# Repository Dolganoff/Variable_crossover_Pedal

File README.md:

Variable_crossover_Pedal
========================

Variable crossover Pedal
For more details refer to http://www.dolganoff.com/fr/tag/crossover/

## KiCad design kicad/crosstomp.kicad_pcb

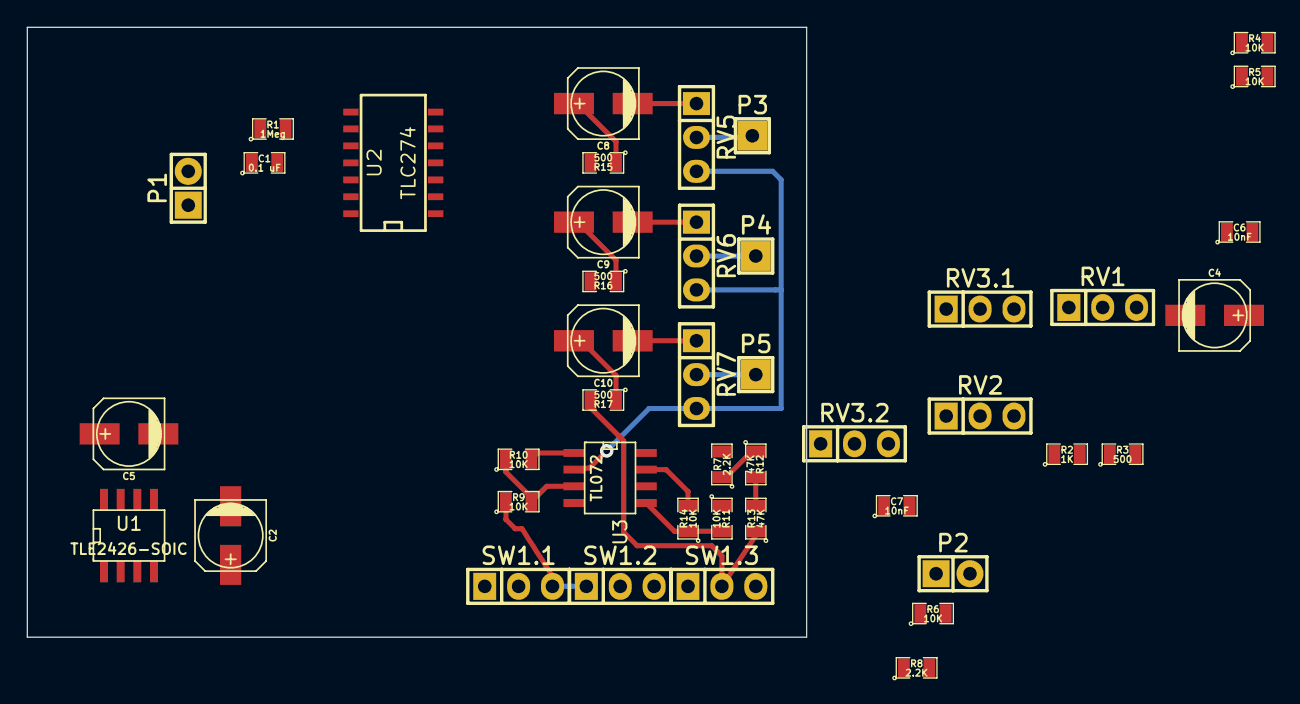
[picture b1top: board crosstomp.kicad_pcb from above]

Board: 2 copper layers, 58.4 x 45.7 mm, 44 parts (0 on the bottom side), 35 nets.

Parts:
C1: 0.1 uF; SMD-0805
C2, C4, C8, C9, C10: 10 uF; c_elec_5x5.3
C5: 1 uF; c_elec_5x5.3
C6, C7: 10nF; SMD-0805
P1: IN; Pin_Header_Straight_1x02
P2: 9V; Pin_Header_Straight_1x02
P3: HIGH; Pin_Header_Straight_1x01
P4: SUM; Pin_Header_Straight_1x01
P5: LOW; Pin_Header_Straight_1x01
R1: 1Meg; SMD-0805
R2: 1K; SMD-0805
R3, R15, R16, R17: 500; SMD-0805
R4, R5, R6, R9, R10, R11, R14: 10K; SMD-0805
R7, R8: 2.2K; SMD-0805
R12, R13: 47K; SMD-0805
RV1, RV2: B 25K; Pin_Header_Straight_1x03
RV3.1, RV3.2: C 100K; Pin_Header_Straight_1x03
RV5, RV6, RV7: A 10K; Pin_Header_Straight_1x03
SW1.1, SW1.2, SW1.3: SW-SPDT; Pin_Header_Straight_1x03
U1: TLE2426-SOIC; SOIC-8_N
U2: TLC274; SOIC-14_N
U3: TL072; SOIC-8_N

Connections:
GND: C2.1, C4.2, P1.1, R1.1, R11.1, RV2.1, RV2.2, RV5.3, RV6.3, RV7.3, SW1.1.2, U1.1, U2.9, U2.13, U3.2
unnamed: C1.1, R1.2, U2.3
unnamed: C1.2, P1.2
unnamed: C5.1, U1.8
unnamed: C6.1, R6.2, R8.1, U2.8
unnamed: C6.2, RV3.1.3, U2.10
unnamed: C7.1, R4.2, SW1.2.2, U2.14
unnamed: C7.2, RV3.2.3, U2.12
unnamed: C8.1, R15.1
unnamed: C8.2, RV5.1
unnamed: C9.1, R16.1
unnamed: C9.2, RV6.1
unnamed: C10.1, R17.1
unnamed: C10.2, RV7.1
unnamed: P3.1, RV5.2
unnamed: P4.1, RV6.2
unnamed: P5.1, RV7.2
unnamed: R2.1, U2.1, U2.2
unnamed: R2.2, RV1.1, RV1.2
unnamed: R3.1, R6.1, U2.6
unnamed: R3.2, RV2.3
unnamed: R4.1, R5.1, RV1.3, U2.5
unnamed: R7.2, RV3.1.1, RV3.1.2
unnamed: R8.2, RV3.2.1, RV3.2.2
unnamed: R9.1, SW1.1.3, SW1.2.1
unnamed: R9.2, R10.1, U3.3
unnamed: R10.2, SW1.3.1, U3.1
unnamed: R11.2, R14.1, U3.5
unnamed: R5.2, R7.1, R12.1, R15.2, U2.7
unnamed: R12.2, R13.2, U3.6
unnamed: R13.1, R17.2, SW1.3.2
unnamed: R14.2, R16.2, U3.7
unnamed: SW1.2.3, SW1.3.3
V+: C4.1, P2.2, U1.3, U2.11, U3.8
V-: C2.2, C5.2, P2.1, U1.2, U2.4, U3.4

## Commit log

2014-08-08 finalized schematics file
2014-08-19 19/08/2014
2014-08-20 board design
2014-08-24 pcb routed and plots generated
